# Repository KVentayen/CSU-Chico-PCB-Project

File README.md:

<!--

TOGGLE PREVIEW IN VISUAL STUDIO CODE:
    Ctrl + Shift + V

This space is designated for Markdown resources:
    - General Markdown Documentation: https://markdown-guide.readthedocs.io/en/latest/index.html

    - Markdown in Visual Studio Code Documentation: https://code.visualstudio.com/docs/languages/markdown

-->

[Comment]: <> (Inline Comment)
[//]: <> (This is also a comment)
[//]: # (This is also a comment)
<!--
    This is a multiline comment
-->

# Video Reference
The tutorial assembled for this project derive from [KiCad STM32 + USB + Buck Converter PCB Design and JLCPCB Assembly (Update) - Phil's Lab #11](https://www.youtube.com/watch?v=C7-8nUU6e3E) by [Phil's Lab](https://www.youtube.com/@PhilsLab) on [YouTube](https://www.youtube.com)

# Promotional
This workshop may be of interest to the following clubs, organizations, or affiliations
- Senior Capstone Electrical and Computer Engineering
- Senior Capstone Mechanical and Mechatronic Engineering
- Intitute of Elecrical and Electronics Engineers (IEEE)
- AIME
- Wildcat Racing
- Wildcat Formula
- Chico Rocketry and Aerospace Club
- General Electrical and Computer Engineering Classes
- Mechanical Keyboard Club

# General Setting Overview
Meetings will take 1.5 to 2 hours.
Expect the acailable range of meetings to be 11 to 12 in total.

## First Meeting
- Introduce the Project
- Introduce the Software
- Introduce the Resources for the Project

## Follwing Meetings
- Take approximately 30 minutes to go over questions for material from the last meeting
- Start working on next material to progress the knowledge of the students
- For the remainder of the session walkthrough the steps to complete the task, if there are questions or someone needs help attend to them

# Equiptment
## Development
When using KiCad it would be a good idea for students to have the following:
- Computer Mouse
    - It would be a good idea for the speed of assembling circuits
- Charger
    - Just depends on the student's computer's battery life and how much it is used
    - This also means that we would need outlets for everyone who would need to charge their device

# Basic Knowledge
It would be a good idea to ensure that students know the following concepts:
- Nodes (as used in circuits)
    - This is to apply the concept to symbols such as:
        - Global Labels
        - Ground Reference
        - +5V Power Supply
        - +3.3V Power Supply
- Resistor Combinations
    - Calculate Resistors in Parallel
    - Calculate Resistors in Series

# Additional Topics
This is a list of additional topics that would be nice to cover aswell
- EasyEDA: To get more components in to KiCad

# Bill of Materials

## Equiptment
- Soldering Iron
- Third Hand (Hold the Board while soldering)
- Fume Extractor
- Wire Cutters
- Wire Strippers
- Solder Sucker
- Needlenose Pliers

## Resistor Chart
Resistor Values
||||||||
| --- | --- | --- | --- | --- | --- | --- |
| 10 | 12 | 15 | 18 | 22 | 27 | 33 |
| 39 | 47 | 56 | 68 | 89 | 100 | 120 |
| 150 | 180 | 220 | 270 | 330 | 390 | 470 |
| 560 | 680 | 920 | 1K | 1k2 | 1k5 | 1K8 |
| 2K2 | 2K7 | 3K3 | 3k9 | 4K7 | 5K6 | 6K8 |
| 8K2 | 10K | 12K | 15K | 18K | 22K | 27K |
| 33K | 39K | 47K | 56K | 68K | 82K | 100K |
| 120K | 150K | 180K | 220K | 270K | 330K | 390K |
| 470K | 560K | 680K | 820K | 1M | 1M2 | 1M5 |
| 1M8 | 2M2 | 2M7 | 3M3 | 3M9 | 4M7 | 5M6 |

## Operational Amplifier (14-Pin Package)
LF347N (Wide Bandwidth Quad JFET Input Operational Amplifiers)

https://www.ti.com/product/LF347-N

https://www.ti.com/lit/ds/symlink/lf347-n.pdf?ts=1685703512723

TL084CN (JFET-Input Operational Amplifiers)

https://www.mouser.com/ProductDetail/STMicroelectronics/TL084CN?qs=vqk%252BPKT8fSxJW2aTIl98LQ%3D%3D

https://www.mouser.com/datasheet/2/389/tl084ac-1383769.pdf

## Diode
1N4148 Diode

https://datasheetspdf.com/pdf/133245/FairchildSemiconductor/1N4148/1

https://datasheetspdf.com/pdf-file/133245/FairchildSemiconductor/1N4148/1

# PCB Manufacturers
- OSH Park (https://oshpark.com)
- JLC PCB (https://jlcpcb.com)
- PCB Way (https://www.pcbway.com)

# Extra
The Mystery of the Missing Power Pins in KiCad (hackaday): https://hackaday.io/project/165772-recreating-the-jupiter-ace/log/165117-the-mystery-of-the-missing-power-pins-in-kicad

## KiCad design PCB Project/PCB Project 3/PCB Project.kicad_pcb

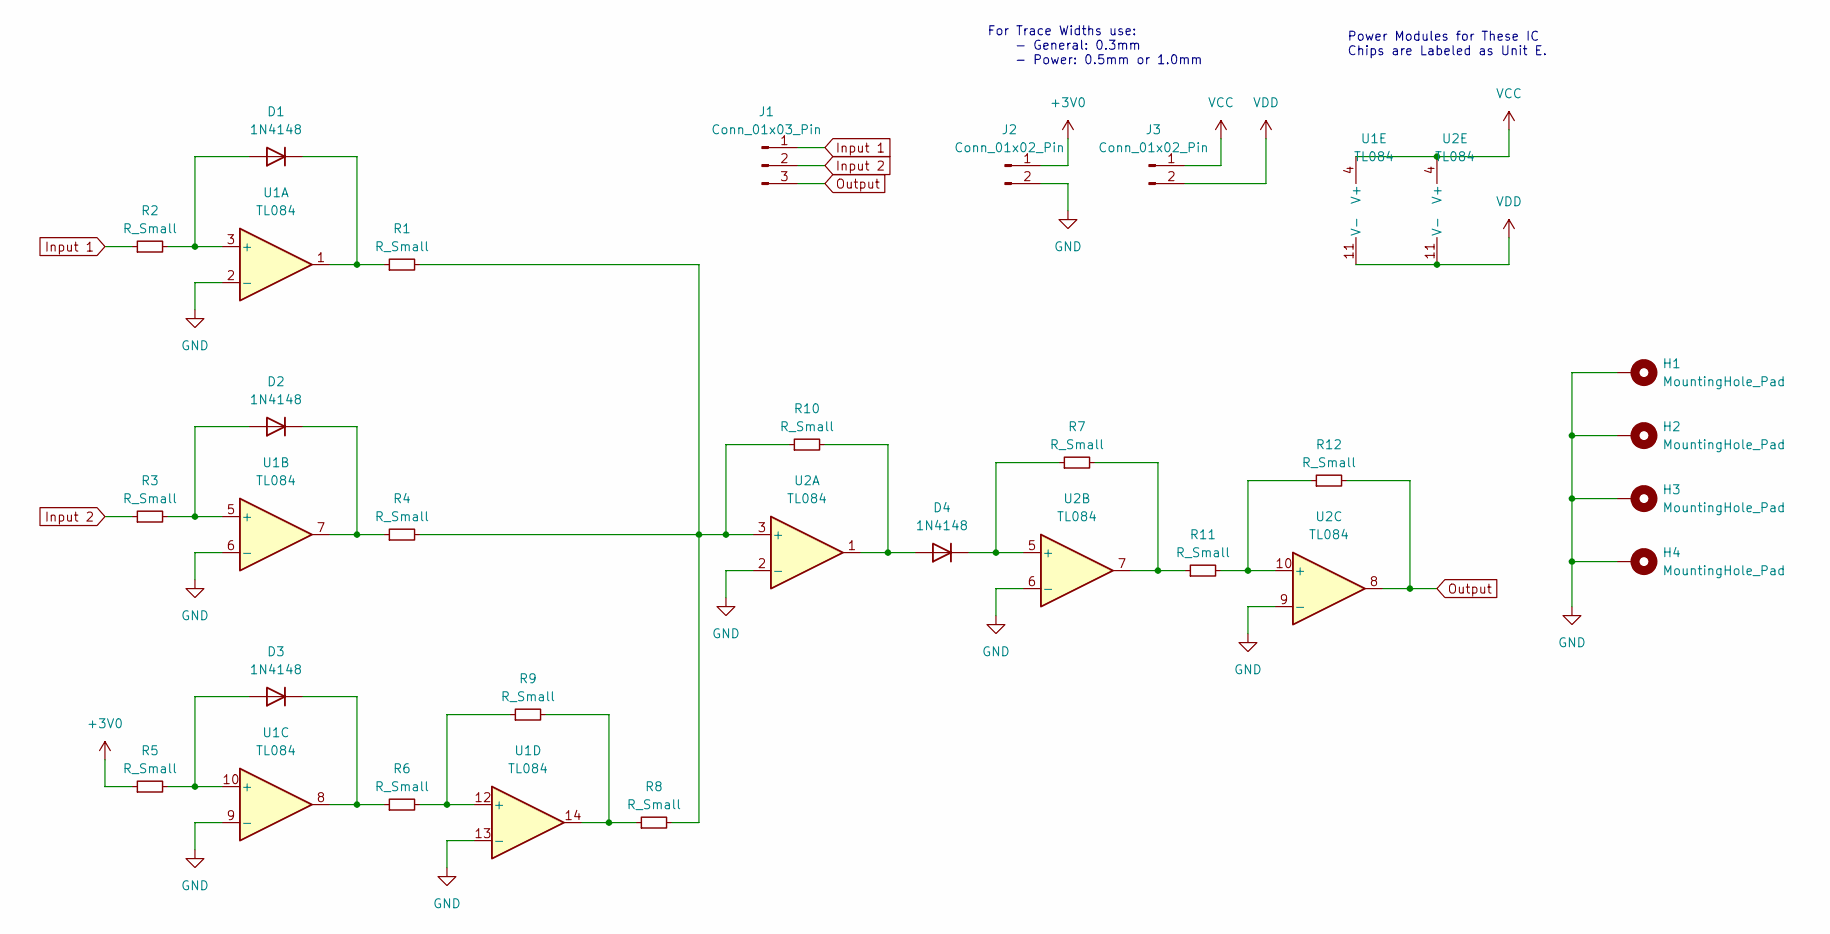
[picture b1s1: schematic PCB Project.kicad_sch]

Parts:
D1, D2, D3, D4: 1N4148; D_DO-35_SOD27_P7.62mm_Horizontal
H1, H2, H3, H4: MountingHole_Pad; MountingHole_3.5mm_Pad_Via
J1: Conn_01x03_Pin; PinHeader_1x03_P2.54mm_Vertical
J2, J3: Conn_01x02_Pin; PinHeader_1x02_P2.54mm_Vertical
R1, R2, R3, R4, R5, R6, R7, R8, R9, R10, R11, R12: R_Small; R_Axial_DIN0411_L9.9mm_D3.6mm_P15.24mm_Horizontal
U1, U2: TL084; DIP-14_W7.62mm_Socket_LongPads

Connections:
+3V0: J2.1, R5.1
GND: H1.1, H2.1, H3.1, H4.1, J2.2, U1.2 (-), U1.6 (-), U1.9 (-), U1.13 (-), U2.2 (-), U2.6 (-), U2.9 (-)
Input 1: J1.1, R2.1
Input 2: J1.2, R3.1
unnamed: D1.2 (A), R2.2, U1.3 (+)
unnamed: D1.1 (K), R1.1, U1.1
unnamed: D2.2 (A), R3.2, U1.5 (+)
unnamed: D2.1 (K), R4.1, U1.7
unnamed: D3.2 (A), R5.2, U1.10 (+)
unnamed: D3.1 (K), R6.1, U1.8
unnamed: D4.2 (A), R10.2, U2.1
unnamed: D4.1 (K), R7.1, U2.5 (+)
unnamed: R8.1, R9.2, U1.14
unnamed: R7.2, R11.1, U2.7
unnamed: R6.2, R9.1, U1.12 (+)
unnamed: R1.2, R4.2, R8.2, R10.1, U2.3 (+)
unnamed: R11.2, R12.1, U2.10 (+)
Output: J1.3, R12.2, U2.8
VCC: J3.1, U1.4 (V+), U2.4 (V+)
VDD: J3.2, U1.11 (V-), U2.11 (V-)

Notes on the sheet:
For Trace Widths use: - General: 0.3mm - Power: 0.5mm or 1.0mm
Power Modules for These IC Chips are Labeled as Unit E.

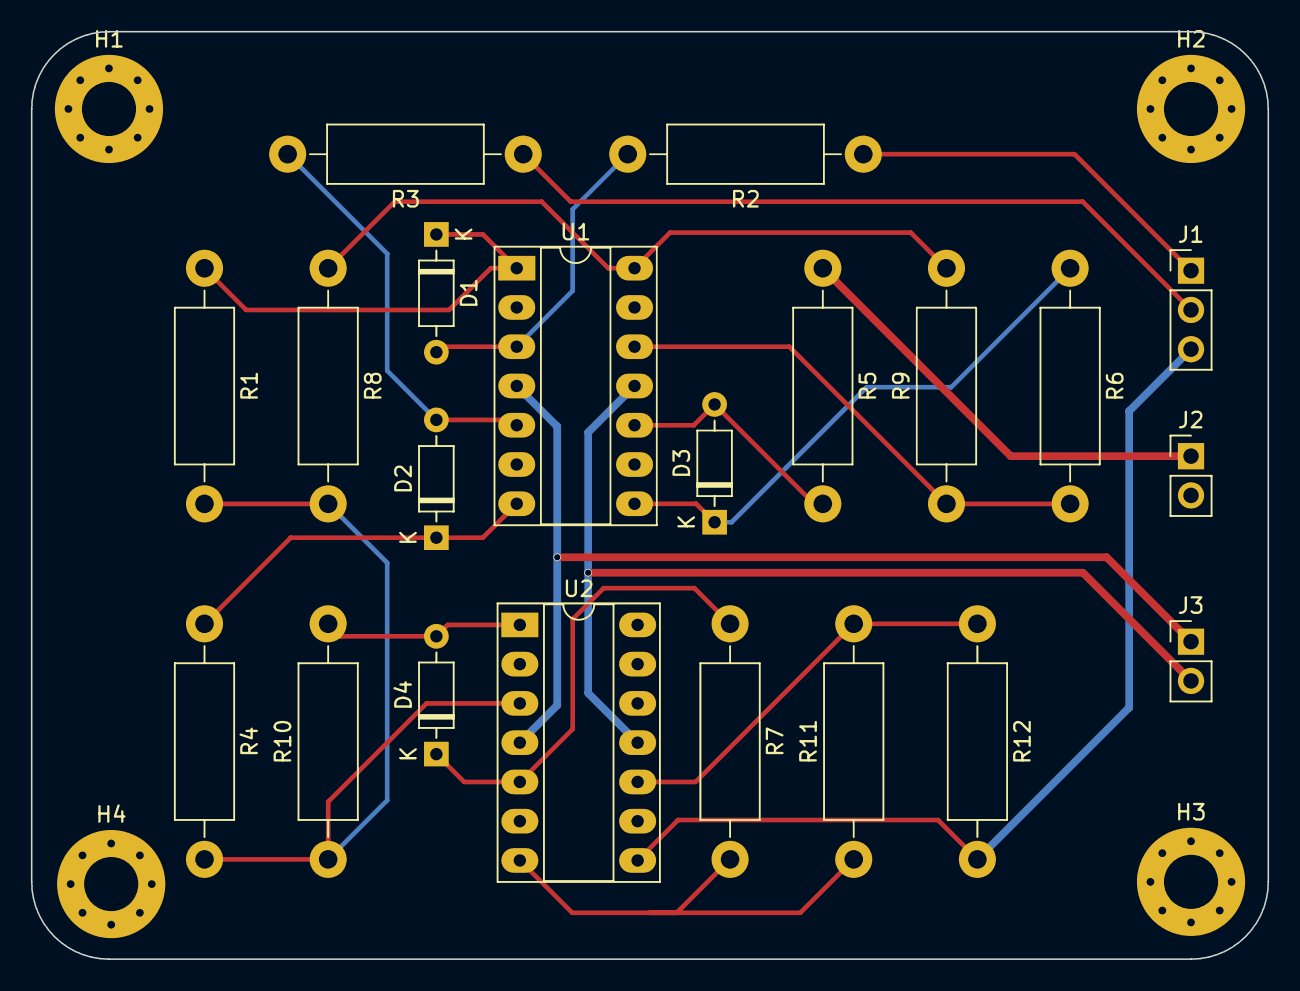
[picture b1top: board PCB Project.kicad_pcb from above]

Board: 2 copper layers, 80.0 x 60.0 mm, 25 parts (0 on the bottom side), 20 nets.

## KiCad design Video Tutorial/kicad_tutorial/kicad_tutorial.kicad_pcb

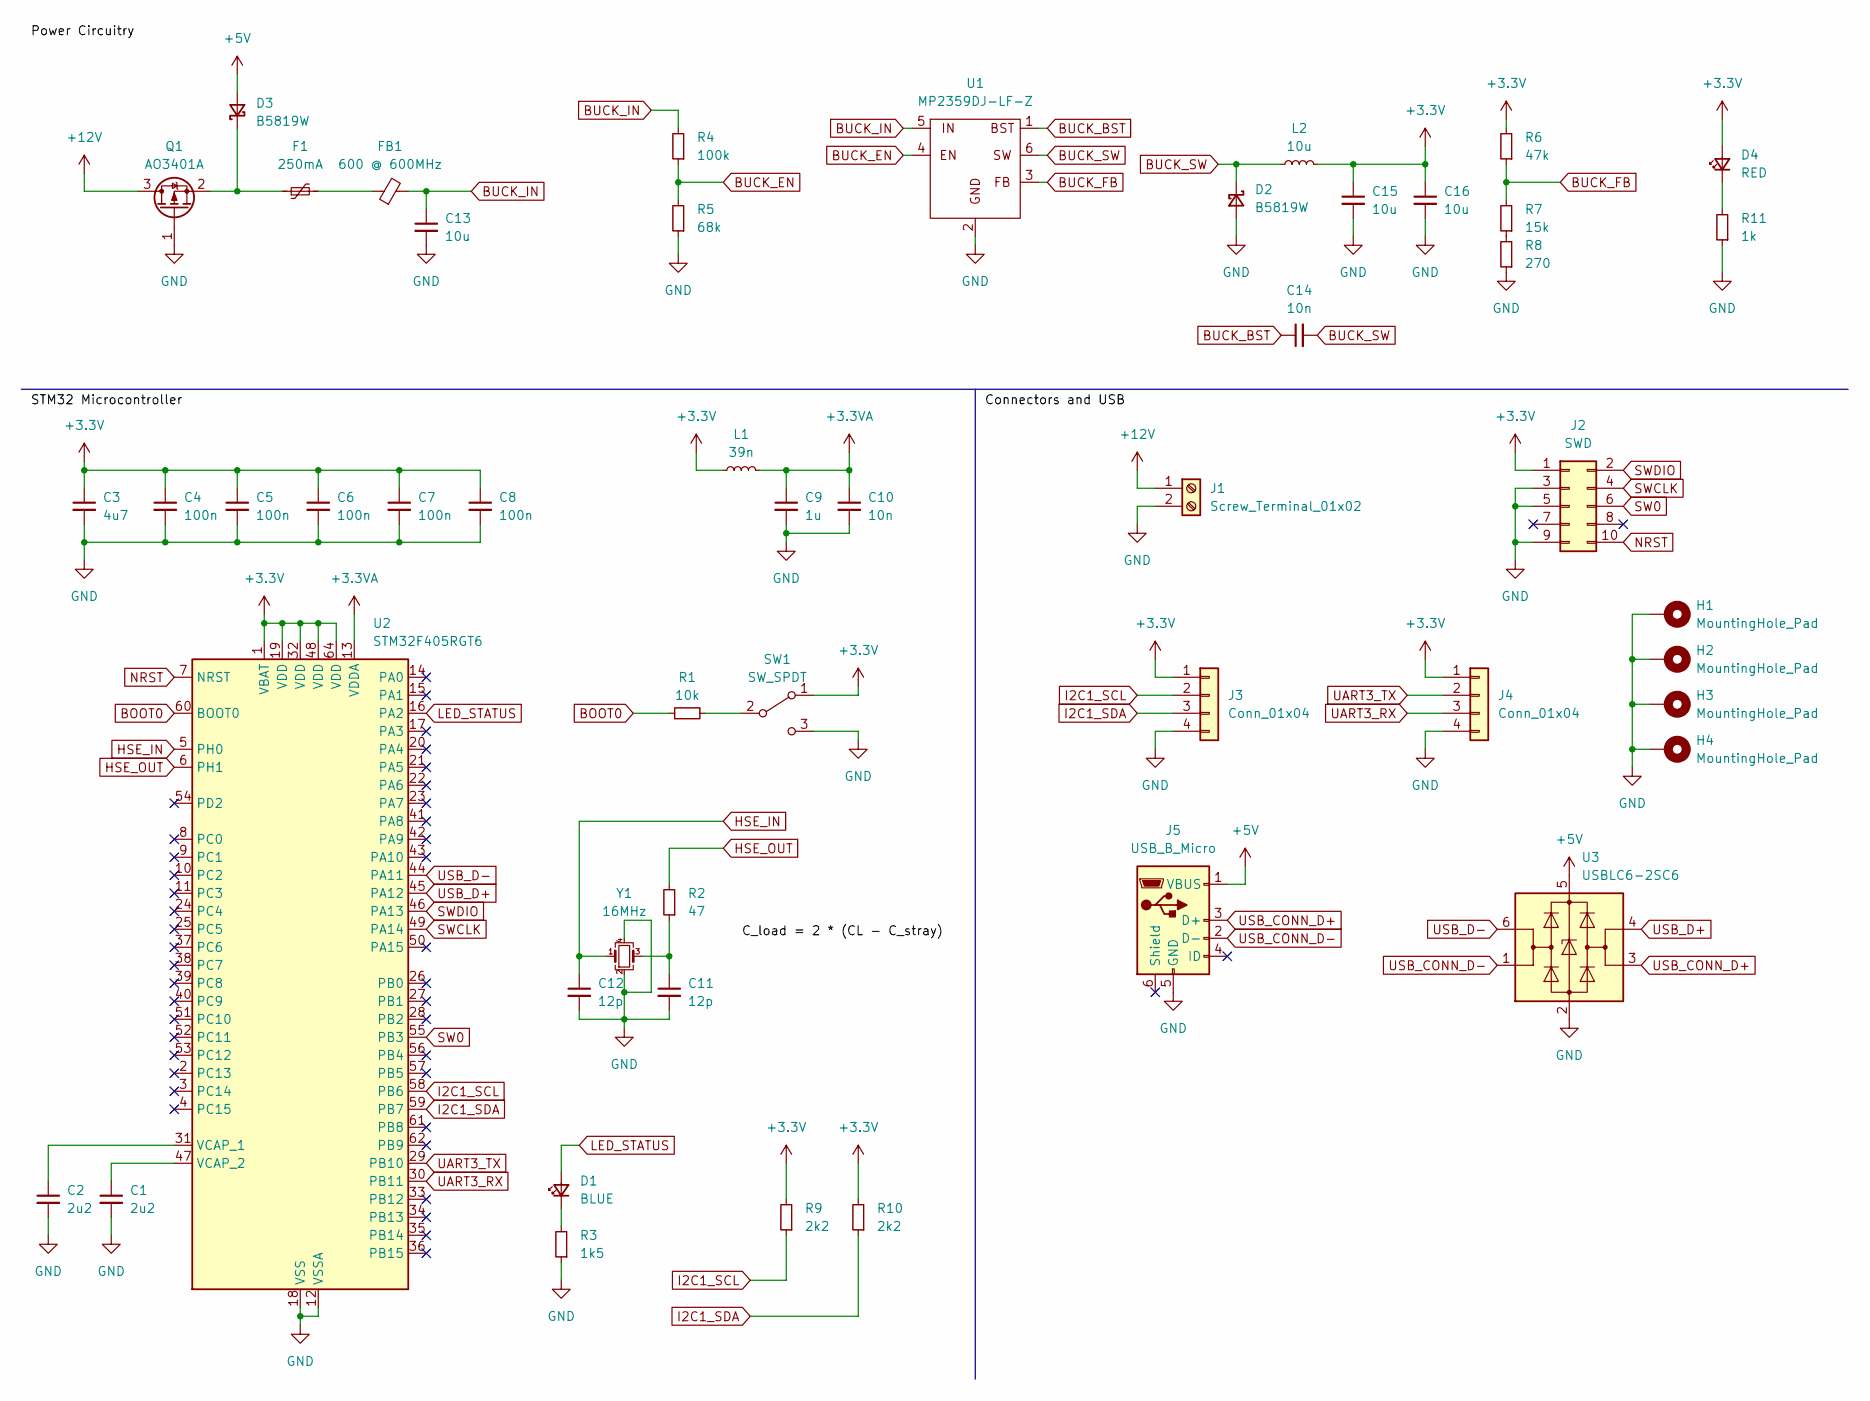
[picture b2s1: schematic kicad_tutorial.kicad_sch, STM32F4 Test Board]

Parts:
C1, C2: 2u2; C_0603_1608Metric; LCSC Part # C23630
C3: 4u7; C_0603_1608Metric; LCSC Part # C19666
C4, C5, C6, C7, C8: 100n; C_0402_1005Metric; LCSC Part # C1525
C9: 1u; C_0402_1005Metric; LCSC Part # C52923
C10: 10n; C_0402_1005Metric; LCSC Part # C15195
C11, C12: 12p; C_0402_1005Metric; LCSC Part # C1547
C13, C15, C16: 10u; C_1206_3216Metric; LCSC Part # C13585
C14: 10n; C_0603_1608Metric; LCSC Part # C15195
D1: BLUE; LED_0603_1608Metric; LCSC Part # C72041
D2, D3: B5819W; D_SOD-123; LCSC Part # C8598
D4: RED; LED_0603_1608Metric; LCSC Part # C2286
F1: 250mA; Fuse_1206_3216Metric; LCSC Part # C369159
FB1: 600 @ 600MHz; L_0805_2012Metric
H1, H2, H3, H4: MountingHole_Pad; MountingHole_4.3mm_M4_Pad_Via
J1: Screw_Terminal_01x02; TerminalBlock_Phoenix_PT-1,5-2-3.5-H_1x02_P3.50mm_Horizontal
J2: SWD; PinHeader_2x05_P1.27mm_Vertical_SMD
J3, J4: Conn_01x04; Molex_PicoBlade_53048-0410_1x04_P1.25mm_Horizontal
J5: USB_B_Micro; USB_Micro-B_GCT_USB3076-30-A
L1: 39n; L_0402_1005Metric; LCSC Part # C26443
L2: 10u; L_Sunlord_MWSA0518S; LCSC Part # C139506
Q1: AO3401A; SOT-23; LCSC Part # C15127
R1: 10k; R_0402_1005Metric; LCSC Part # C25744
R2: 47; R_0402_1005Metric; LCSC Part # C25118
R3: 1k5; R_0603_1608Metric; LCSC Part # C22843
R4: 100k; R_0603_1608Metric; LCSC Part # C25803
R5: 68k; R_0603_1608Metric; LCSC Part # C23231
R6: 47k; R_0603_1608Metric; LCSC Part # C25819
R7: 15k; R_0603_1608Metric; LCSC Part # C22809
R8: 270; R_0603_1608Metric; LCSC Part # C22966
R9, R10: 2k2; R_0402_1005Metric; LCSC Part # C25879
R11: 1k; R_0603_1608Metric; LCSC Part # C21190
SW1: SW_SPDT; SW_SPDT_PCM12
U1: MP2359DJ-LF-Z; SOT-23-6; LCSC Part # C14259
U2: STM32F405RGT6; LQFP-64_10x10mm_P0.5mm; LCSC Part # C15742
U3: USBLC6-2SC6; SOT-23-6; LCSC Part # C7519
Y1: 16MHz; Crystal_SMD_3225-4Pin_3.2x2.5mm; LCSC Part # C13738

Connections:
+3.3V: C3.1, C4.1, C5.1, C6.1, C7.1, C8.1, C15.1, C16.1, D4.2 (A), J2.1, J3.1, J4.1, L1.1, L2.2, R6.2, R9.2, R10.2, SW1.1 (A), U2.1 (VBAT), U2.19 (VDD), U2.32 (VDD), U2.48 (VDD), U2.64 (VDD)
+3.3VA: C9.1, C10.1, L1.2, U2.13 (VDDA)
+5V: D3.2 (A), J5.1 (VBUS), U3.5 (VBUS)
+12V: J1.1, Q1.3 (D)
BOOT0: R1.1, U2.60 (BOOT0)
BUCK_BST: C14.1, U1.1
BUCK_EN: R4.1, R5.2, U1.4
BUCK_FB: R6.1, R7.2, U1.3
BUCK_IN: C13.1, FB1.2, R4.2, U1.5
BUCK_SW: C14.2, D2.1 (K), L2.1, U1.6
GND: C1.2, C2.2, C3.2, C4.2, C5.2, C6.2, C7.2, C8.2, C9.2, C10.2, C11.2, C12.2, C13.2, C15.2, C16.2, D2.2 (A), H1.1, H2.1, H3.1, H4.1, J1.2, J2.3, J2.5, J2.9, J3.4, J4.4, J5.5 (GND), Q1.1 (G), R3.1, R5.1, R8.1, R11.1, SW1.3 (C), U1.2, U2.12 (VSSA), U2.18 (VSS), U2.63 (VSS), U3.2 (GND), Y1.2, Y1.4
HSE_IN: C12.1, U2.5 (PH0), Y1.1
HSE_OUT: R2.2, U2.6 (PH1)
I2C1_SCL: J3.2, R9.1, U2.58 (PB6)
I2C1_SDA: J3.3, R10.1, U2.59 (PB7)
LED_STATUS: D1.2 (A), U2.16 (PA2)
NRST: J2.10, U2.7 (NRST)
unnamed: C11.1, R2.1, Y1.3
unnamed: D1.1 (K), R3.2
unnamed: D3.1 (K), F1.1, Q1.2 (S)
unnamed: D4.1 (K), R11.2
unnamed: F1.2, FB1.1
unnamed: R7.1, R8.2
unnamed: R1.2, SW1.2 (B)
unnamed: C2.1, U2.31 (VCAP_1)
unnamed: C1.1, U2.47 (VCAP_2)
SW0: J2.6, U2.55 (PB3)
SWCLK: J2.4, U2.49 (PA14)
SWDIO: J2.2, U2.46 (PA13)
UART3_RX: J4.3, U2.30 (PB11)
UART3_TX: J4.2, U2.29 (PB10)
USB_CONN_D+: J5.3 (D+), U3.3 (I/O2)
USB_CONN_D-: J5.2 (D-), U3.1 (I/O1)
USB_D+: U2.45 (PA12), U3.4 (I/O2)
USB_D-: U2.44 (PA11), U3.6 (I/O1)

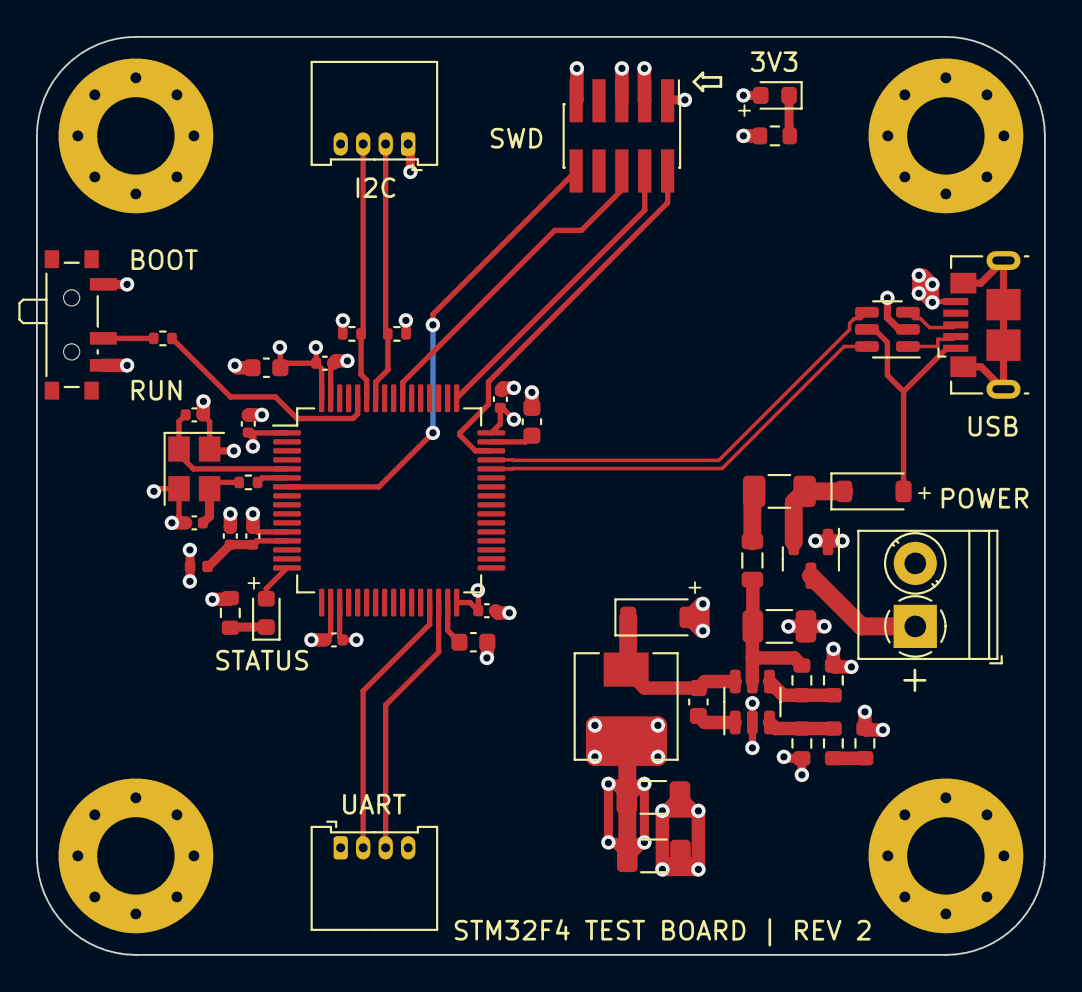
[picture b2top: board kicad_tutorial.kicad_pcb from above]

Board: 4 copper layers, 56.0 x 51.0 mm, 50 parts (0 on the bottom side), 35 nets.

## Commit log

2023-06-02 Added Datasheets to Repository
2023-06-03 Updaded BOM and Separated Resistor Calculations.
2023-06-04 Added details about the KiCad video (Phil's Lab).
2023-06-04 Completed video before Chapter: Decoupling capacitors
2023-06-04 Added notes for Chapter: 'No connect' flags
2023-06-05 Added notes for Chapter: Buck converter circuitry
2023-06-06 Added Suggestions to README.md
2023-06-06 Added notes for Chapter: USB
2023-06-06 Added Mechanical Keyboard Club to Promotional
2023-06-07 Added Additional Topics to README.md
2023-06-07 Added notes for Chapter: Design Rules
2023-06-07 Minor Change in KiCad files
2023-06-08 Added notes for Chapter: Rough layout, finer details
2023-06-08 Added Equiptment Section
2023-06-09 Added notes for Chapter: Improving the layout, finer details
2023-06-09 Added notes for Chapter: Tombstoning
2023-06-10 Added notes for Chapter: Design rules checker (DRC)
2023-06-13 Completed KiCad Tutorial Video
2023-06-23 Added .gitignore file
2023-06-23 Started writing PCB Project Description
2023-06-23 Moved videoNotes.md
2023-06-30 Updated Project Description files
2023-06-30 Updated Project Description files.
2023-06-30 Updated material for the PCB Workshop.
2023-07-06 Added Notes discussed with Yolie.
2023-07-06 Started KiCad Project.
2023-07-06 Moved TeX.gitignore
2023-07-06 Added a description of an Analog Multiplier.
2023-07-26 Worked on project deliverables.
2023-07-27 Added Extra to the README.md
2023-07-28 Added traces to power the IC Chips.
2023-07-29 Added Sections to Repository
2023-08-02 Added descriptions.
2023-08-02 Added Appendixes and Descriptions to Schematic Layout and PCB Board Layout
